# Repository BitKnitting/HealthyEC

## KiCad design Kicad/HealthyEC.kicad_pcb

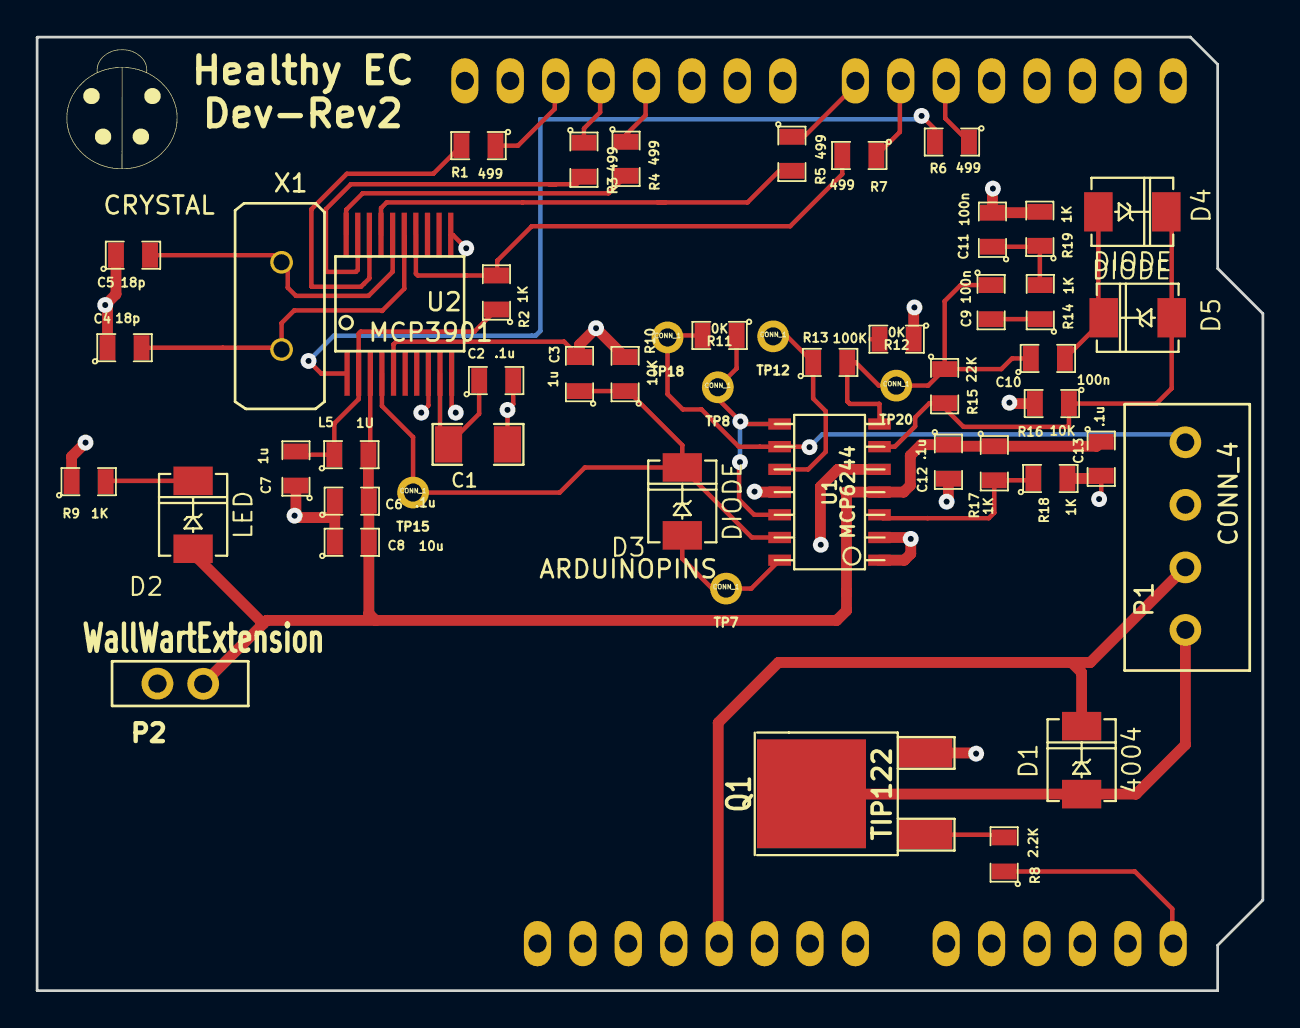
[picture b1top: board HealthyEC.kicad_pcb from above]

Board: 2 copper layers, 68.6 x 53.3 mm, 51 parts (0 on the bottom side), 36 nets.

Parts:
ARD1: ARDUINOPINS; ArduinoLettuceBuddy
C1: 10u; SM1206
C2, C6, C12, C13: .1u; SM0805
C3, C7: 1u; SM0805
C4, C5: 18p; SM0805
C8: 10u; SM0805
C9, C10, C11: 100n; SM0805
D1: 4004; DO-214AC(SMA)
D2: LED; DO-214AC(SMA)
D3, D4, D5: DIODE; DO-214AC(SMA)
L5: 1U; SM0805
P1: CONN_4; LB_4PosTB
P2: WallWartExtension; LB_2TB
Q1: TIP122; DPAK2
R1, R3, R4, R5, R6, R7: 499; SM0805
R2, R9, R14, R17, R18, R19: 1K; SM0805
R8: 2.2K; SM0805
R10, R16: 10K; SM0805
R11, R12: 0K; SM0805
R13: 100K; SM0805
R15: 22K; SM0805
TP7, TP8, TP12, TP15, TP18, TP20: CONN_1; LB_TestPoint
U1: MCP6244; so-14
U2: MCP3901; LB_MCP3901
X1: CRYSTAL; LB_Crystal

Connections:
/Arduino/ECPump: ARD1.10, R8.1
/Arduino/MISO: ARD1.23, R3.1
/Arduino/MOSI: ARD1.22, R4.1
/Arduino/SCLK: ARD1.24, R1.1
/Arduino/V+_ARD: ARD1.1, D1.2, P1.2
/Arduino/~CS: ARD1.18, R5.1
/Arduino/~DR: ARD1.17, R7.1
/Arduino/~RESET: ARD1.16, R6.1
/DigitalAccess/DVdd: C7.2, L5.1, R2.1, U2.2
/DigitalAccess/EC_Meas: C3.1, D3.2, R10.1, TP15.1, U1.13, U2.4
/DigitalAccess/MISO_ISO: R3.2, U2.19
/DigitalAccess/MOSI_ISO: R4.2, U2.20
/DigitalAccess/OSC1: C4.2, U2.15, X1.2
/DigitalAccess/OSC2: C5.2, U2.16, X1.1
/DigitalAccess/REFIN: C1.1, C2.1, U2.9
/DigitalAccess/SCLK_ISO: R1.2, U2.18
/DigitalAccess/V+_WallWart: C6.2, C8.2, C12.1, C13.1, D2.1, L5.2, P2.2, R17.1, U1.4, U2.3
/DigitalAccess/VGND: C3.2, C11.2, P1.3, R10.2, R12.1, R16.2, R19.2, U1.1, U1.2, U1.5, U2.5
/DigitalAccess/~CS_ISO: R5.2, U2.17
/DigitalAccess/~DR: R2.2, R7.2, U2.14
/DigitalAccess/~RESET: R6.2, U2.1
/EC/EC_Probe+: P1.4, R11.2, TP18.1, U1.9
/EC/G1: C10.2, D4.1, D5.2
/EC/f1: C9.2, R14.1
/EC/f2: C11.1, R14.2, R19.1
/EC/pin 3: R17.2, R18.1, U1.3
/EC/pin 6: D4.2, D5.1, R15.2, R16.1, U1.6
/EC/pin 7: C9.1, C10.1, R13.2, R15.1, TP20.1, U1.7
/EC/pin 14: D3.1, TP7.1, U1.14
/Healthy pH Shield/LED: D2.2, R9.2
/Pumps/SW_ECPump: D1.1, P1.1, Q1.2
AC_Shrunk: R12.2, R13.1, TP12.1, U1.10
AGND: C1.2, C2.2, C4.1, C5.1, C6.1, C7.1, C8.1, C12.2, C13.2, P2.1, R9.1, R18.2, U1.11, U2.8, U2.10, U2.11
EC_Signal: R11.1, TP8.1, U1.8, U1.12
GND: ARD1.2, ARD1.3, Q1.3
unnamed: Q1.1, R8.2

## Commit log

2014-08-25 first check in
2014-08-27 updated after 8/25 feedback
2014-08-30 added spice files
2014-09-01 pushing any changes
2014-09-01 making sure changes to EC Floating GND LTSPice are in
2014-09-15 updated EC circuit
2014-09-16 Ready for 1st Review
2014-09-18 Ready for Review
2014-09-19 Ready for layout review
2014-09-22 moved some of the component text from under a component in the layout
2014-09-23 added Gerbers sent to OshPark
2014-10-29 Dev-Rev2 sent to OshPark
2014-10-29 Cleaned up for Dev-Rev2
2014-11-14 Started changes for Dev-Rev3
